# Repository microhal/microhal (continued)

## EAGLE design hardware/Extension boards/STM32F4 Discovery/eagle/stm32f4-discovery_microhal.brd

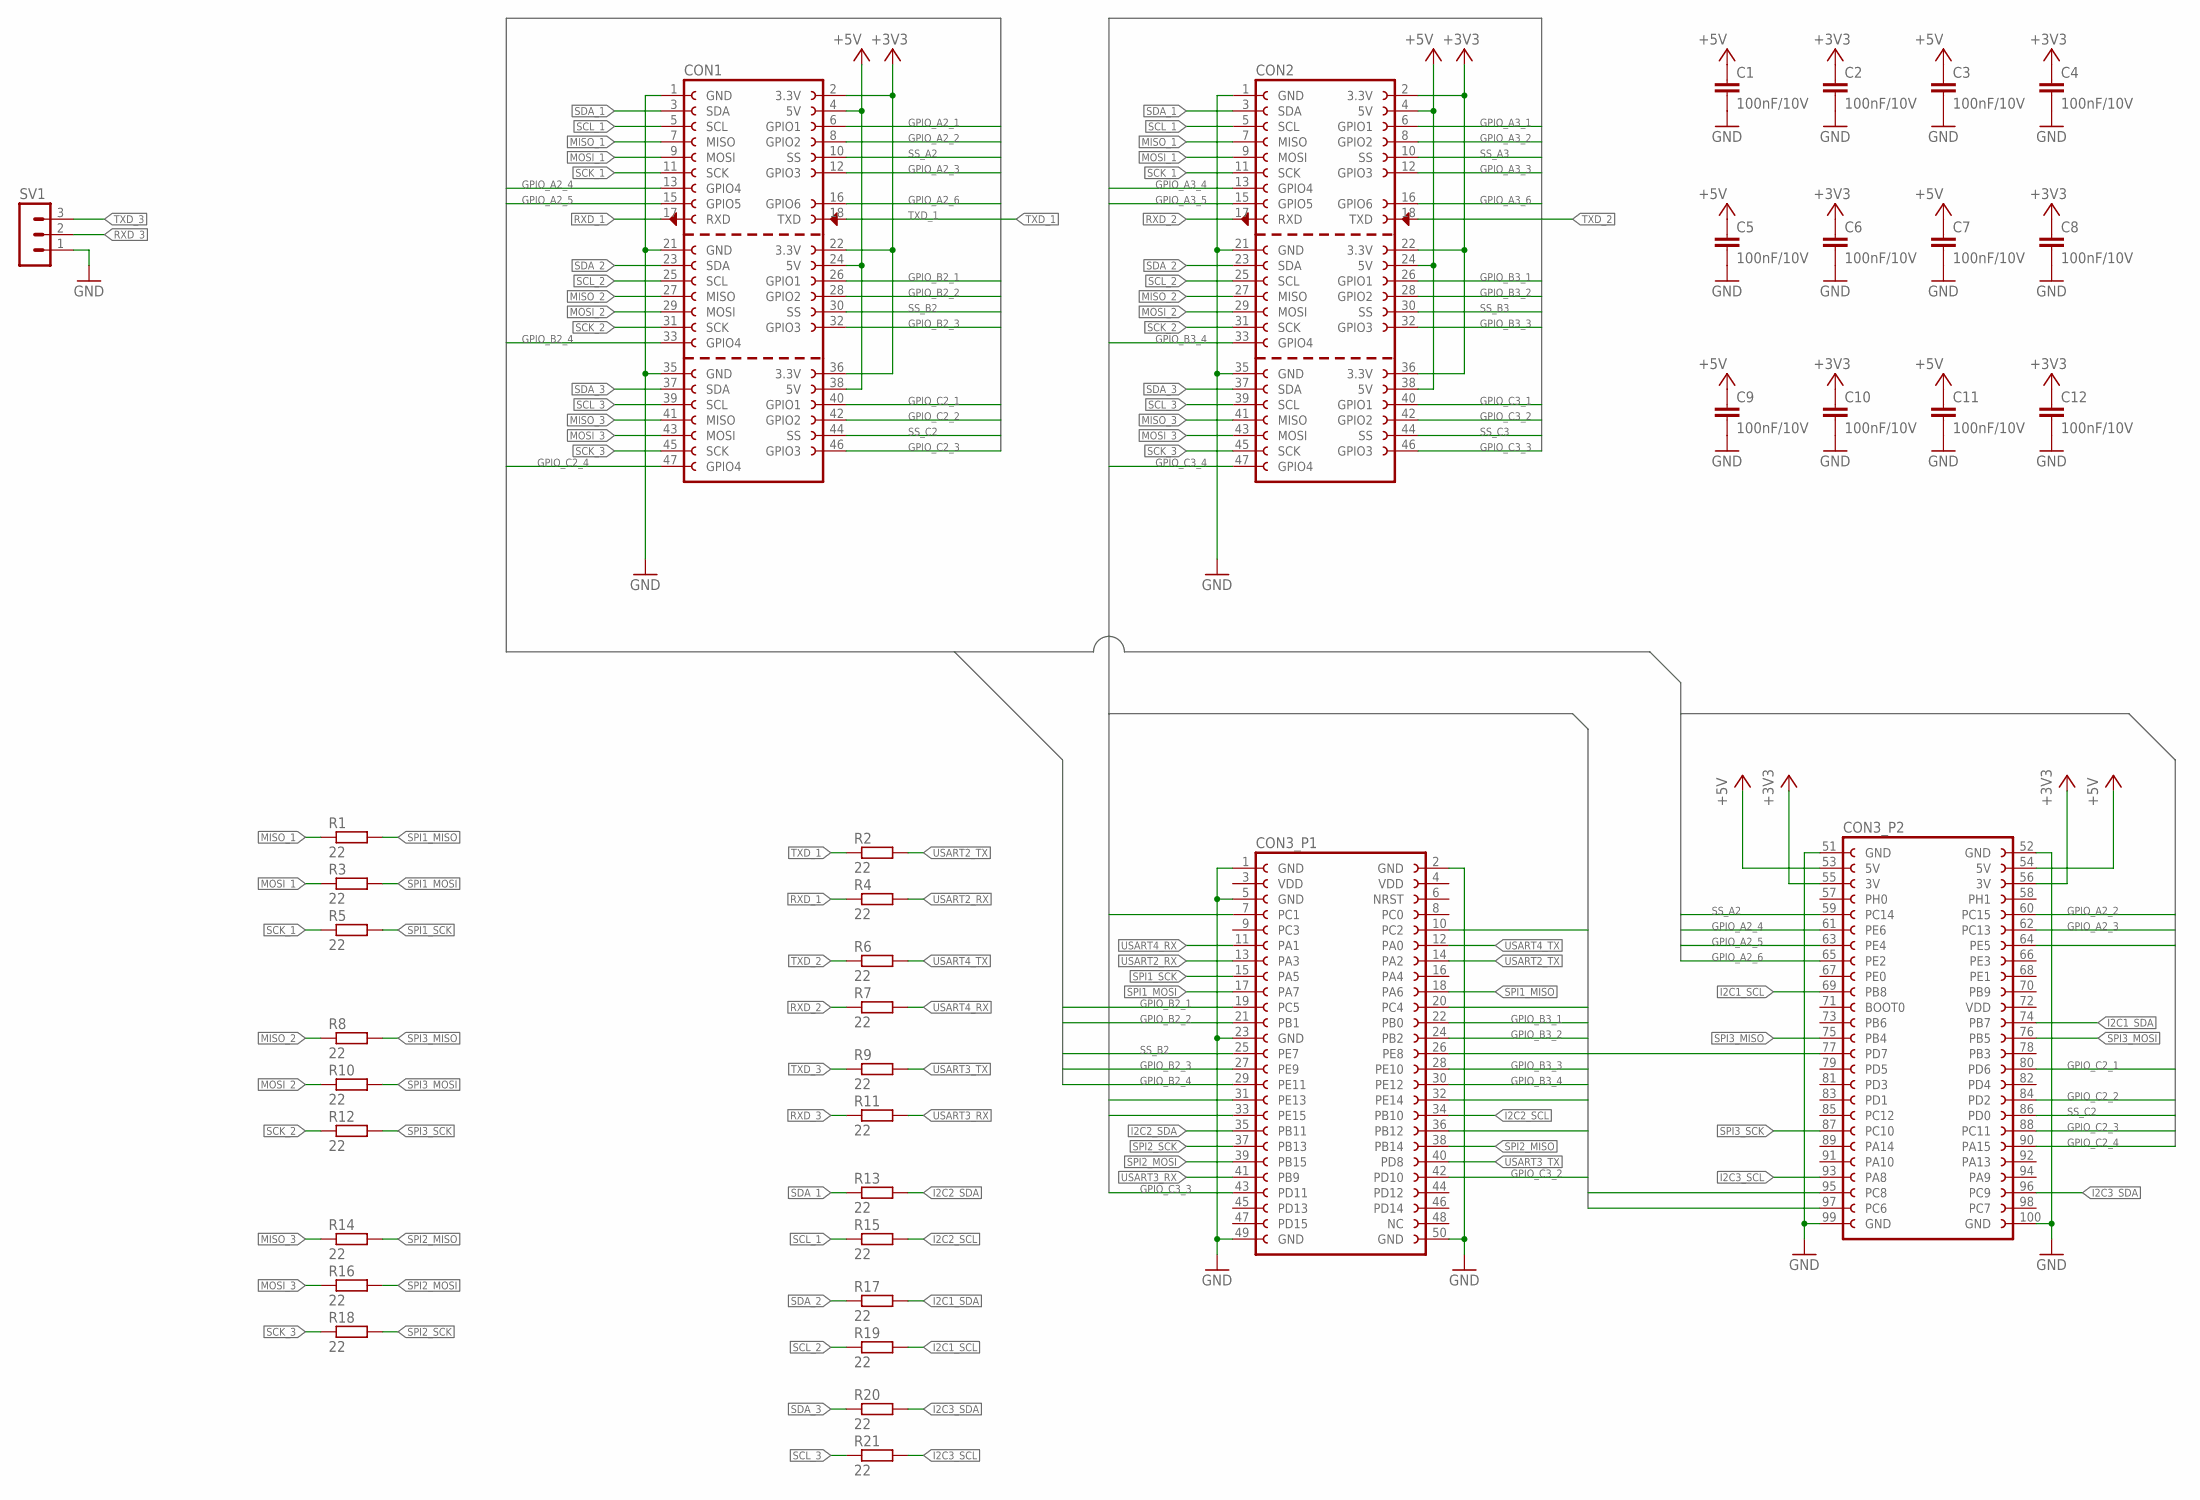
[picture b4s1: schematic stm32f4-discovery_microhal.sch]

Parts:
C1, C2, C3, C4, C5, C6, C7, C8, C9, C10, C11, C12: 100nF/10V; C0603K
CON1, CON2: MICROHAL_CONNECTOR_F_3
CON3: STM32F4DISCOVERY-CONNECTOR; STM32F4DISCOVERY_CONNECTOR
R1, R2, R3, R4, R5, R6, R7, R8, R9, R10, R11, R12, R13, R14, R15, R16, R17, R18, R19, R20, R21: 22; R0603
SV1: MA03-1

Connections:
+3V3: C2.1, C4.1, C6.1, C8.1, C10.1, C12.1, CON1.2 (3.3V), CON1.22 (3.3V), CON1.36 (3.3V), CON2.2 (3.3V), CON2.22 (3.3V), CON2.36 (3.3V), CON3.55 (3V), CON3.56 (3V)
+5V: C1.1, C3.1, C5.1, C7.1, C9.1, C11.1, CON1.4 (5V), CON1.24 (5V), CON1.38 (5V), CON2.4 (5V), CON2.24 (5V), CON2.38 (5V), CON3.53 (5V), CON3.54 (5V)
GND: C1.2, C2.2, C3.2, C4.2, C5.2, C6.2, C7.2, C8.2, C9.2, C10.2, C11.2, C12.2, CON1.1 (GND), CON1.21 (GND), CON1.35 (GND), CON2.1 (GND), CON2.21 (GND), CON2.35 (GND), CON3.1 (GND), CON3.2 (GND), CON3.5 (GND), CON3.23 (GND), CON3.49 (GND), CON3.50 (GND), CON3.51 (GND), CON3.52 (GND), CON3.99 (GND), CON3.100 (GND), SV1.1
GPIO_A2_1: CON1.6 (GPIO1), CON3.64 (PE5)
GPIO_A2_2: CON1.8 (GPIO2), CON3.60 (PC15)
GPIO_A2_3: CON1.12 (GPIO3), CON3.62 (PC13)
GPIO_A2_4: CON1.13 (GPIO4), CON3.61 (PE6)
GPIO_A2_5: CON1.15 (GPIO5), CON3.63 (PE4)
GPIO_A2_6: CON1.16 (GPIO6), CON3.65 (PE2)
GPIO_A3_1: CON2.6 (GPIO1), CON3.97 (PC6)
GPIO_A3_2: CON2.8 (GPIO2), CON3.31 (PE13)
GPIO_A3_3: CON2.12 (GPIO3), CON3.7 (PC1)
GPIO_A3_4: CON2.13 (GPIO4), CON3.10 (PC2)
GPIO_A3_5: CON2.15 (GPIO5), CON3.20 (PC4)
GPIO_A3_6: CON2.16 (GPIO6), CON3.77 (PD7)
GPIO_B2_1: CON1.26 (GPIO1), CON3.19 (PC5)
GPIO_B2_2: CON1.28 (GPIO2), CON3.21 (PB1)
GPIO_B2_3: CON1.32 (GPIO3), CON3.27 (PE9)
GPIO_B2_4: CON1.33 (GPIO4), CON3.29 (PE11)
GPIO_B3_1: CON2.26 (GPIO1), CON3.22 (PB0)
GPIO_B3_2: CON2.28 (GPIO2), CON3.24 (PB2)
GPIO_B3_3: CON2.32 (GPIO3), CON3.28 (PE10)
GPIO_B3_4: CON2.33 (GPIO4), CON3.30 (PE12)
GPIO_C2_1: CON1.40 (GPIO1), CON3.80 (PD6)
GPIO_C2_2: CON1.42 (GPIO2), CON3.84 (PD2)
GPIO_C2_3: CON1.46 (GPIO3), CON3.88 (PC11)
GPIO_C2_4: CON1.47 (GPIO4), CON3.90 (PA15)
GPIO_C3_1: CON2.40 (GPIO1), CON3.32 (PE14)
GPIO_C3_2: CON2.42 (GPIO2), CON3.42 (PD10)
GPIO_C3_3: CON2.46 (GPIO3), CON3.43 (PD11)
GPIO_C3_4: CON2.47 (GPIO4), CON3.95 (PC8)
I2C1_SCL: CON3.69 (PB8), R19.2
I2C1_SDA: CON3.74 (PB7), R17.2
I2C2_SCL: CON3.34 (PB10), R15.2
I2C2_SDA: CON3.35 (PB11), R13.2
I2C3_SCL: CON3.93 (PA8), R21.2
I2C3_SDA: CON3.96 (PC9), R20.2
MISO_1: CON1.7 (MISO), CON2.7 (MISO), R1.1
MISO_2: CON1.27 (MISO), CON2.27 (MISO), R8.1
MISO_3: CON1.41 (MISO), CON2.41 (MISO), R14.1
MOSI_1: CON1.9 (MOSI), CON2.9 (MOSI), R3.1
MOSI_2: CON1.29 (MOSI), CON2.29 (MOSI), R10.1
MOSI_3: CON1.43 (MOSI), CON2.43 (MOSI), R16.1
RXD_1: CON1.17 (RXD), R4.1
RXD_2: CON2.17 (RXD), R7.1
RXD_3: R11.1, SV1.2
SCK_1: CON1.11 (SCK), CON2.11 (SCK), R5.1
SCK_2: CON1.31 (SCK), CON2.31 (SCK), R12.1
SCK_3: CON1.45 (SCK), CON2.45 (SCK), R18.1
SCL_1: CON1.5 (SCL), CON2.5 (SCL), R15.1
SCL_2: CON1.25 (SCL), CON2.25 (SCL), R19.1
SCL_3: CON1.39 (SCL), CON2.39 (SCL), R21.1
SDA_1: CON1.3 (SDA), CON2.3 (SDA), R13.1
SDA_2: CON1.23 (SDA), CON2.23 (SDA), R17.1
SDA_3: CON1.37 (SDA), CON2.37 (SDA), R20.1
SPI1_MISO: CON3.18 (PA6), R1.2
SPI1_MOSI: CON3.17 (PA7), R3.2
SPI1_SCK: CON3.15 (PA5), R5.2
SPI2_MISO: CON3.38 (PB14), R14.2
SPI2_MOSI: CON3.39 (PB15), R16.2
SPI2_SCK: CON3.37 (PB13), R18.2
SPI3_MISO: CON3.75 (PB4), R8.2
SPI3_MOSI: CON3.76 (PB5), R10.2
SPI3_SCK: CON3.87 (PC10), R12.2
SS_A2: CON1.10 (SS), CON3.59 (PC14)
SS_A3: CON2.10 (SS), CON3.33 (PE15)
SS_B2: CON1.30 (SS), CON3.25 (PE7)
SS_B3: CON2.30 (SS), CON3.26 (PE8)
SS_C2: CON1.44 (SS), CON3.86 (PD0)
SS_C3: CON2.44 (SS), CON3.36 (PB12)
TXD_1: CON1.18 (TXD), R2.1
TXD_2: CON2.18 (TXD), R6.1
TXD_3: R9.1, SV1.3
USART2_RX: CON3.13 (PA3), R4.2
USART2_TX: CON3.14 (PA2), R2.2
USART3_RX: CON3.41 (PB9), R11.2
USART3_TX: CON3.40 (PD8), R9.2
USART4_RX: CON3.11 (PA1), R7.2
USART4_TX: CON3.12 (PA0), R6.2

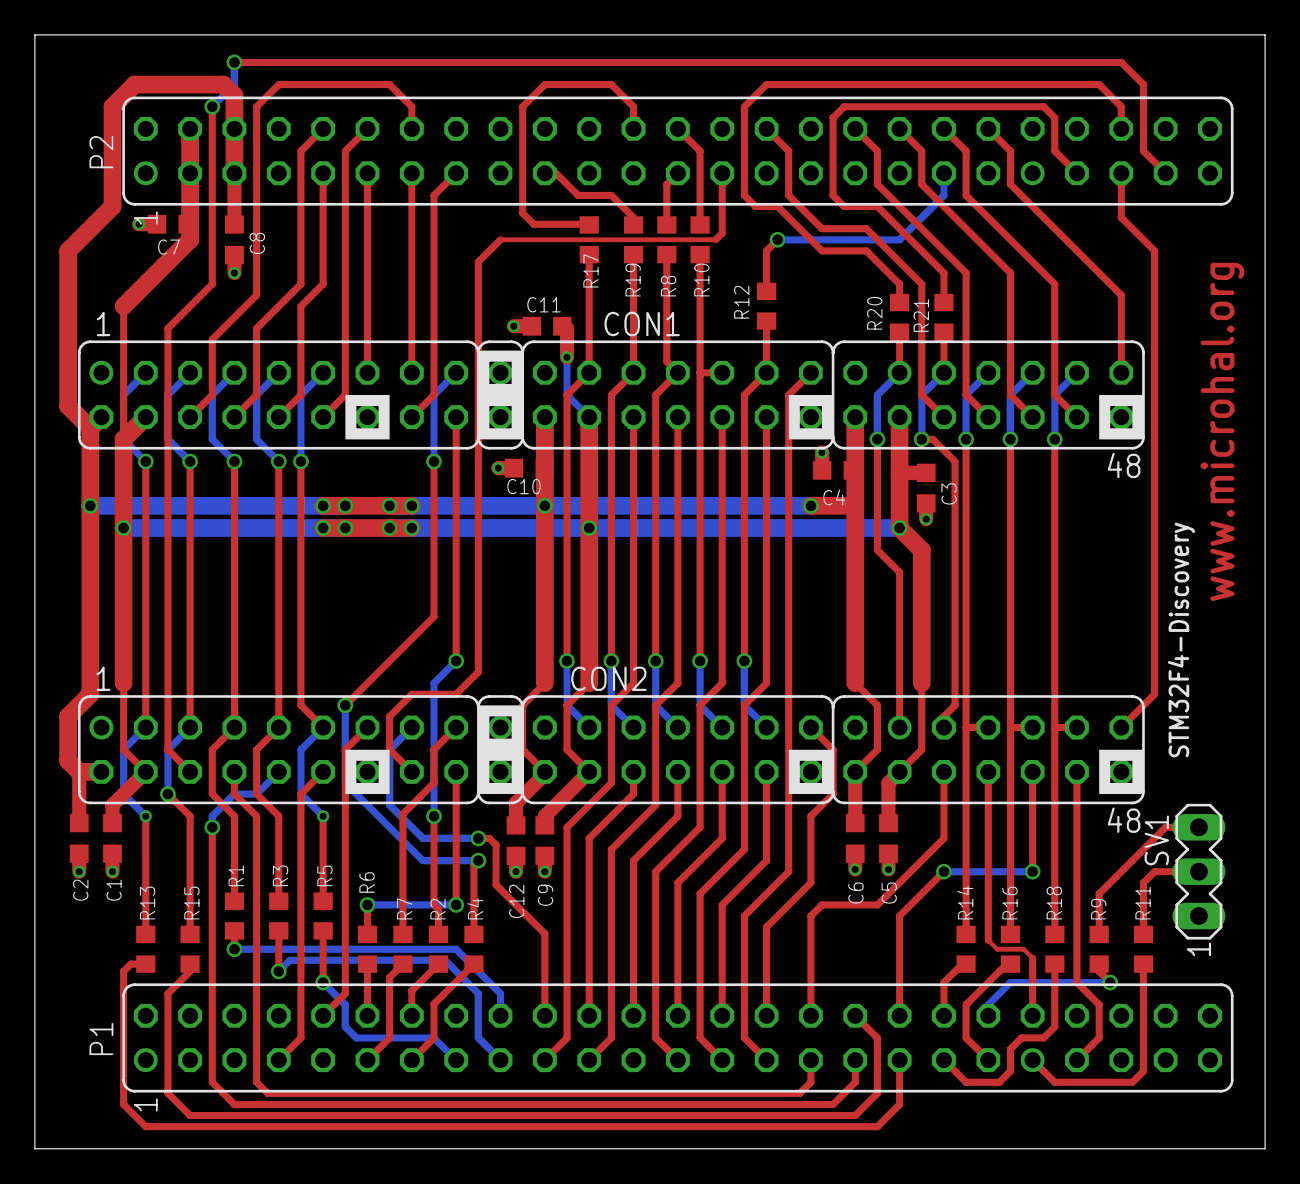
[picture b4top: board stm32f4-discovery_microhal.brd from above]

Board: 2 copper layers, 70.5 x 63.8 mm, 37 parts (0 on the bottom side), 79 nets.

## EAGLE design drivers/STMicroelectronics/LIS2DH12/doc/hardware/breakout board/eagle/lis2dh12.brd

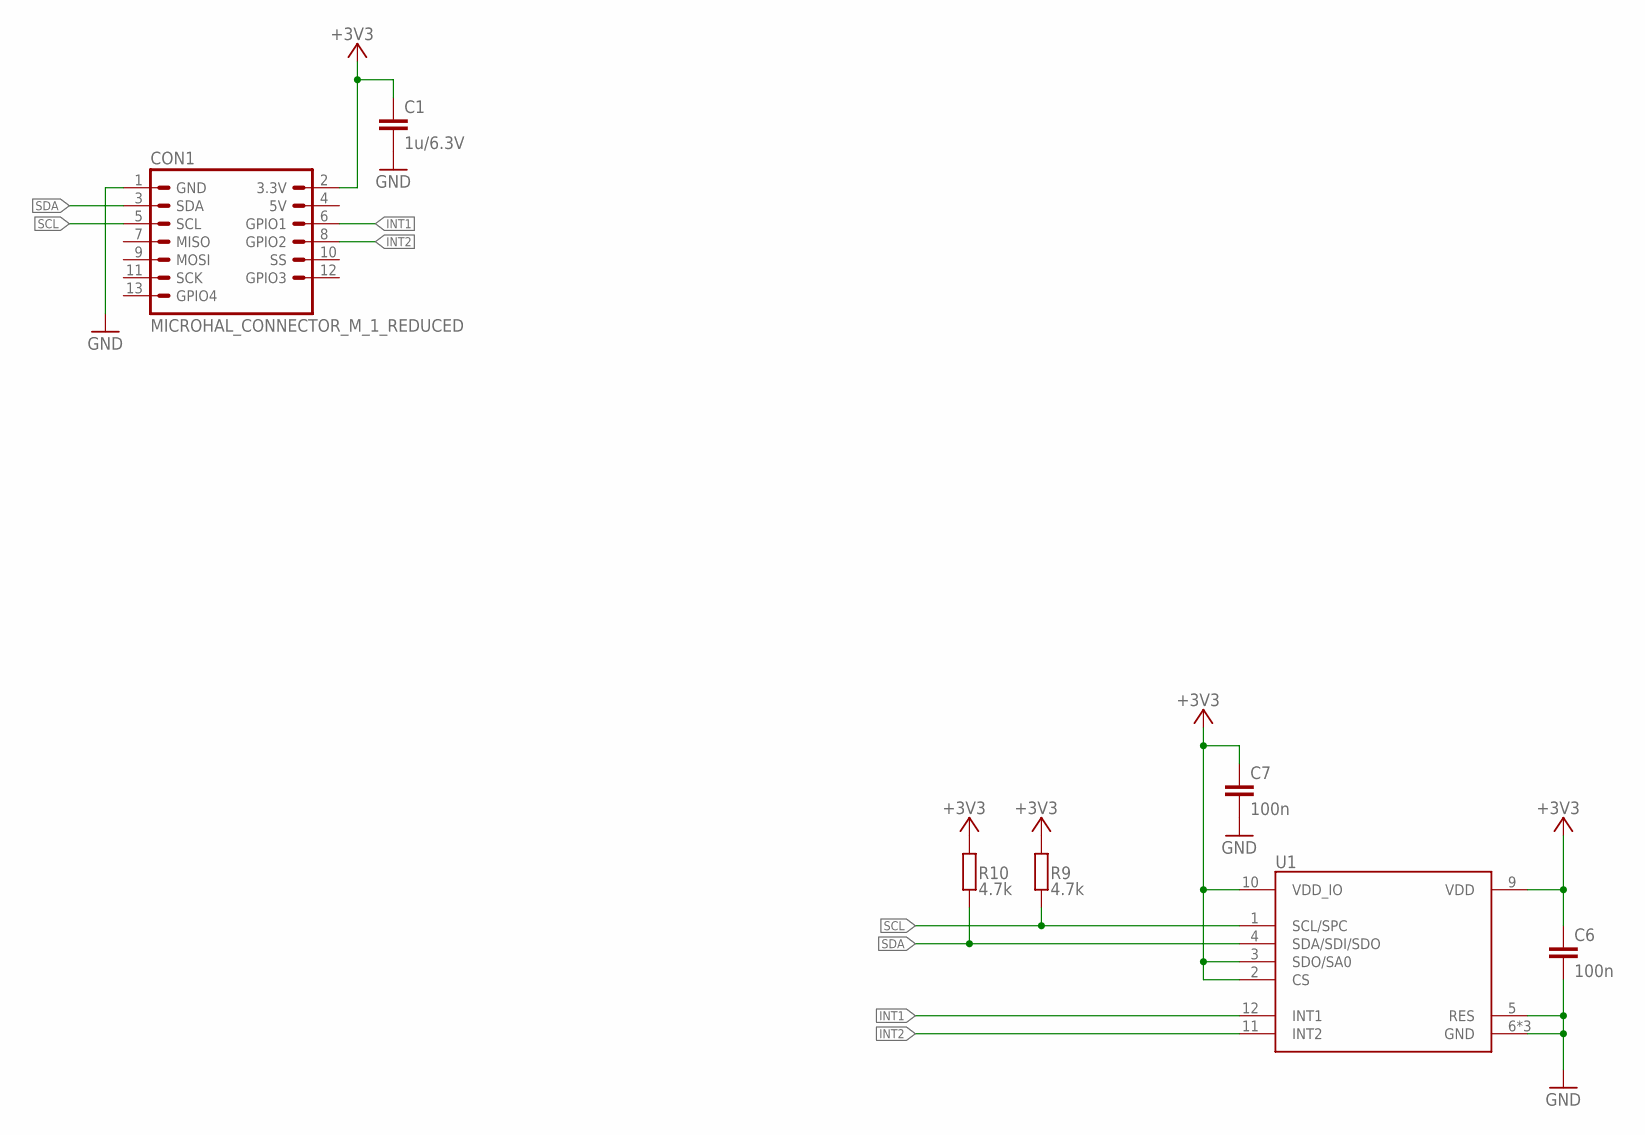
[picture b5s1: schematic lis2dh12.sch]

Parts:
C1: 1u/6.3V; C0603K
C6, C7: 100n; C0603K
CON1: MICROHAL_CONNECTOR_M_1_REDUCED; MICROHAL_CONNECTOR_M_1_REDUCED_EDGE
R9, R10: 4.7k; R0603
U1: LIS2DH12; LGA-12

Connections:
+3V3: C1.1, C6.1, C7.1, CON1.2 (3.3V), R9.1, R10.1, U1.2 (CS), U1.3 (SDO/SA0), U1.9 (VDD), U1.10 (VDD_IO)
GND: C1.2, C6.2, C7.2, CON1.1 (GND), U1.5 (RES), U1.6 (GND), U1.7 (GND), U1.8 (GND)
INT1: CON1.6 (GPIO1), U1.12 (INT1)
INT2: CON1.8 (GPIO2), U1.11 (INT2)
SCL: CON1.5 (SCL), R9.2, U1.1 (SCL/SPC)
SDA: CON1.3 (SDA), R10.2, U1.4 (SDA/SDI/SDO)

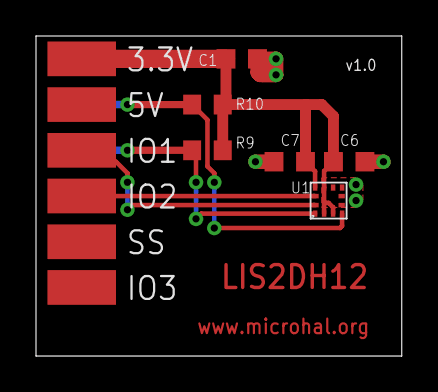
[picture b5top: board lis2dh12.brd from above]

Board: 2 copper layers, 20.3 x 17.8 mm, 7 parts (0 on the bottom side), 6 nets.

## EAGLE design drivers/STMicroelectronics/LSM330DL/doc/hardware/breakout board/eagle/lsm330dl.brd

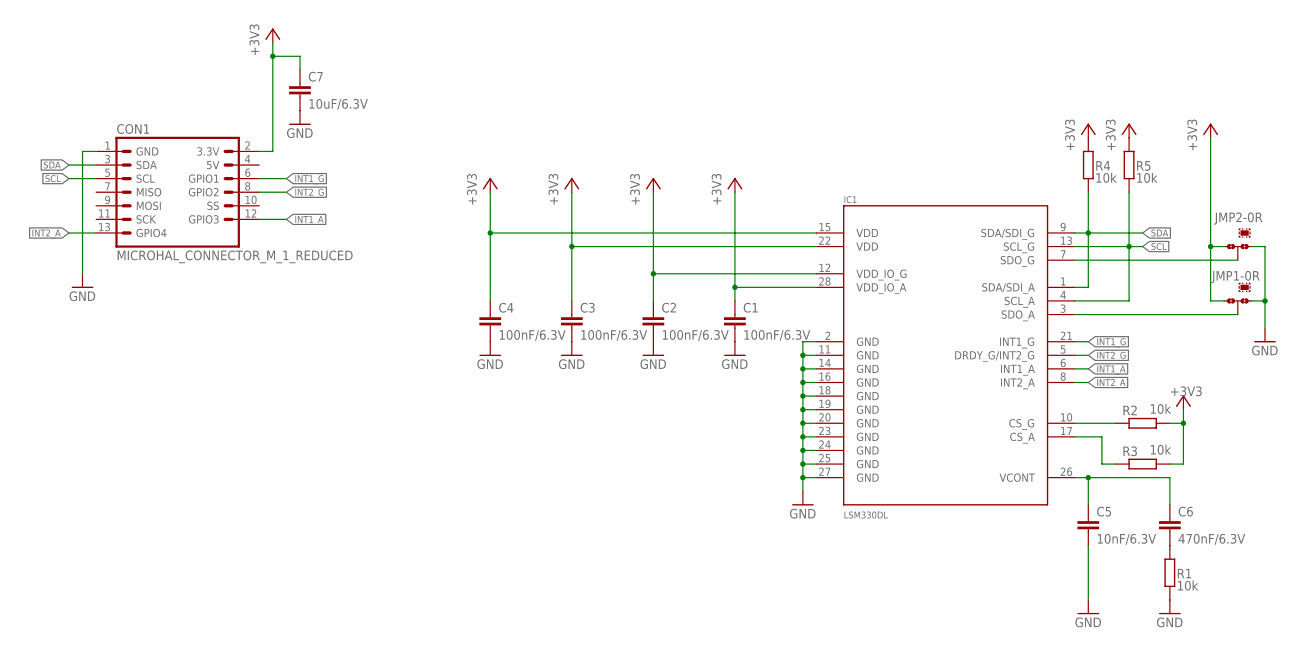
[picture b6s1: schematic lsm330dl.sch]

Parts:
C1, C2, C3, C4: 100nF/6.3V; C0402K
C5: 10nF/6.3V; C0402K
C6: 470nF/6.3V; C0402K
C7: 10uF/6.3V; C0805K
CON1: MICROHAL_CONNECTOR_M_1_REDUCED; MICROHAL_CONNECTOR_M_1_REDUCED_EDGE
IC1: LSM330DL; LGA7.5X4.4_28L
JMP1, JMP2: 0R-JUMPC; C0R-JMP
R1, R2, R3, R4, R5: 10k; R0402

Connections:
+3V3: C1.1, C2.1, C3.1, C4.1, C7.1, CON1.2 (3.3V), IC1.12 (VDD_IO_G), IC1.15 (VDD), IC1.22 (VDD), IC1.28 (VDD_IO_A), JMP1.3, JMP2.3, R2.1, R3.1, R4.2, R5.2
GND: C1.2, C2.2, C3.2, C4.2, C5.2, C7.2, CON1.1 (GND), IC1.2 (GND), IC1.11 (GND), IC1.14 (GND), IC1.16 (GND), IC1.18 (GND), IC1.19 (GND), IC1.20 (GND), IC1.23 (GND), IC1.24 (GND), IC1.25 (GND), IC1.27 (GND), JMP1.1, JMP2.1, R1.1
INT1_A: CON1.12 (GPIO3), IC1.6 (INT1_A)
INT1_G: CON1.6 (GPIO1), IC1.21 (INT1_G)
INT2_A: CON1.13 (GPIO4), IC1.8 (INT2_A)
INT2_G: CON1.8 (GPIO2), IC1.5 (DRDY_G/INT2_G)
unnamed: C6.2, R1.2
unnamed: C5.1, C6.1, IC1.26 (VCONT)
unnamed: IC1.17 (CS_A), R3.2
unnamed: IC1.10 (CS_G), R2.2
unnamed: IC1.3 (SDO_A), JMP1.2
unnamed: IC1.7 (SDO_G), JMP2.2
SCL: CON1.5 (SCL), IC1.4 (SCL_A), IC1.13 (SCL_G), R5.1
SDA: CON1.3 (SDA), IC1.1 (SDA/SDI_A), IC1.9 (SDA/SDI_G), R4.1

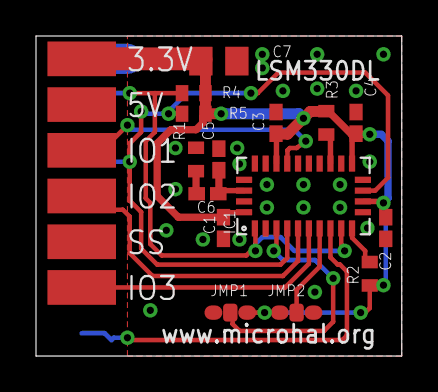
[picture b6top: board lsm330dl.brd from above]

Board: 2 copper layers, 20.3 x 17.8 mm, 16 parts (0 on the bottom side), 14 nets.

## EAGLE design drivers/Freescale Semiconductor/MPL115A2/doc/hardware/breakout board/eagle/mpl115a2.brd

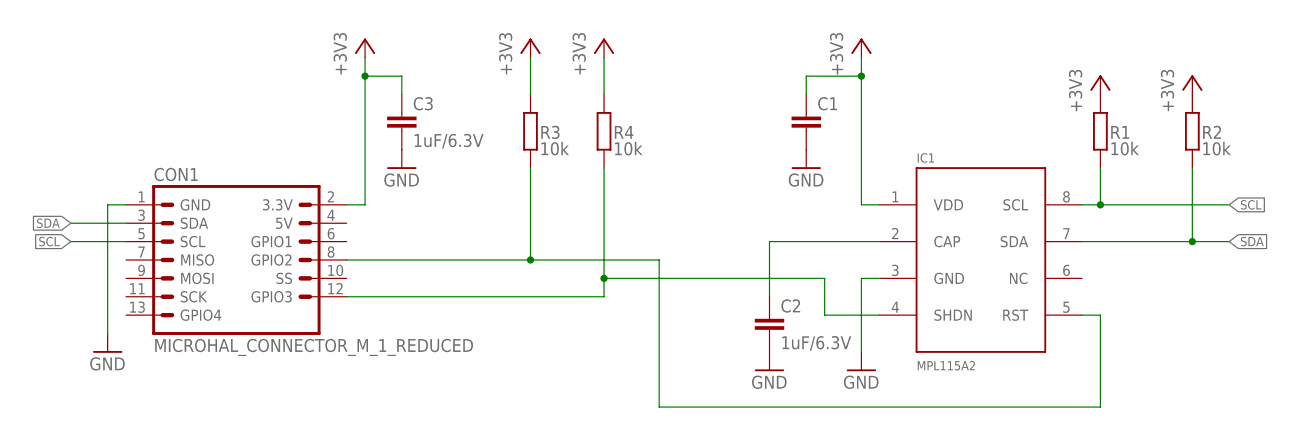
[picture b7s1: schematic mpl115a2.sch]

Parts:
C1: C-EUC0603K; C0603K
C2, C3: 1uF/6.3V; C0603K
CON1: MICROHAL_CONNECTOR_M_1_REDUCED; MICROHAL_CONNECTOR_M_1_REDUCED_EDGE
IC1: MPL115A2
R1, R2, R3, R4: 10k; R0603

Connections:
+3V3: C1.1, C3.1, CON1.2 (3.3V), IC1.1 (VDD), R1.2, R2.2, R3.2, R4.2
GND: C1.2, C2.2, C3.2, CON1.1 (GND), IC1.3 (GND)
unnamed: CON1.12 (GPIO3), IC1.4 (SHDN), R4.1
unnamed: C2.1, IC1.2 (CAP)
unnamed: CON1.8 (GPIO2), IC1.5 (RST), R3.1
SCL: CON1.5 (SCL), IC1.8 (SCL), R1.1
SDA: CON1.3 (SDA), IC1.7 (SDA), R2.1

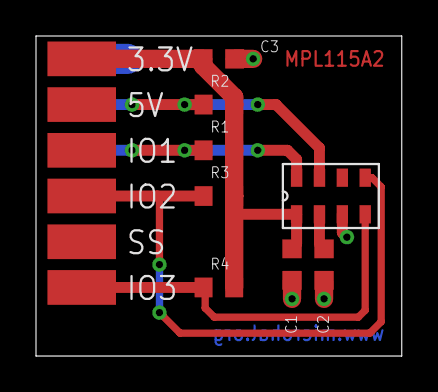
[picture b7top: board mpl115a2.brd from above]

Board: 2 copper layers, 20.3 x 17.8 mm, 9 parts (0 on the bottom side), 7 nets.

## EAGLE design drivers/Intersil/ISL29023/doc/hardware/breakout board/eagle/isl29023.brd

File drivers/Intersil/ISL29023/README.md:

# ISL29023
Integrated Digital Light Sensor with Interrupt

[Documentation PDF](http://www.intersil.com/content/dam/Intersil/documents/isl2/isl29023.pdf)

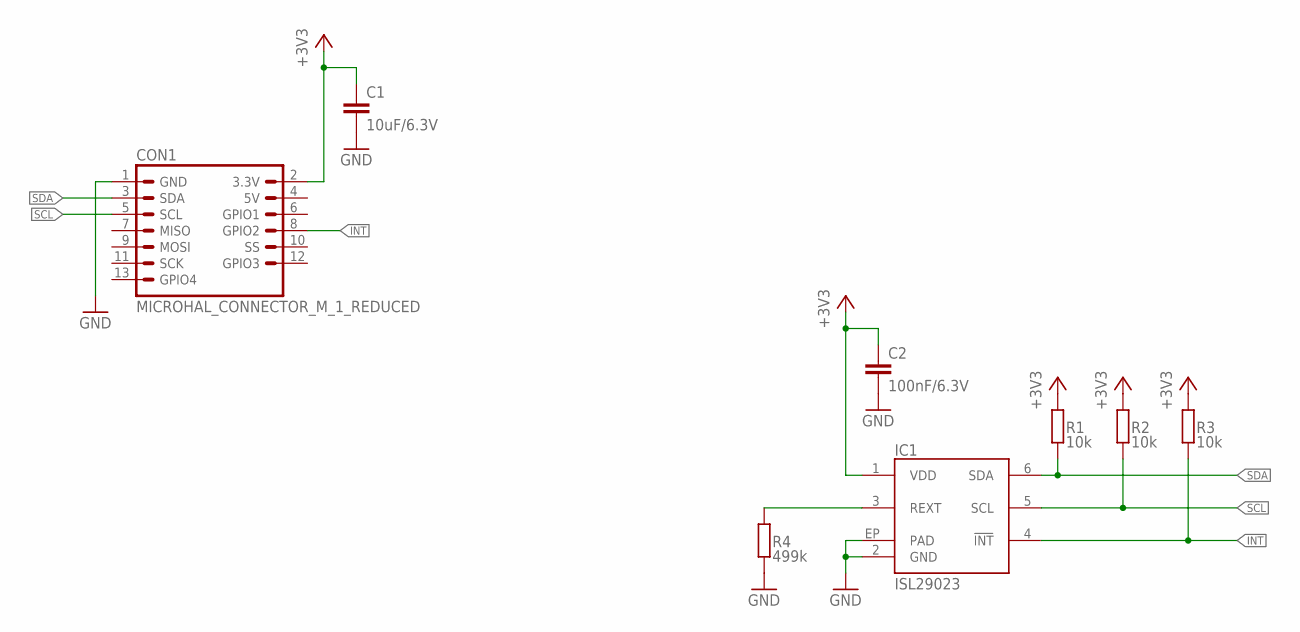
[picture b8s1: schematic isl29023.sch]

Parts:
C1: 10uF/6.3V; C0805K
C2: 100nF/6.3V; C0603K
CON1: MICROHAL_CONNECTOR_M_1_REDUCED; MICROHAL_CONNECTOR_M_1_REDUCED_EDGE
IC1: ISL29023; ODFN-6
R1, R2, R3: 10k; R0603
R4: 499k; R0603

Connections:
+3V3: C1.1, C2.1, CON1.2 (3.3V), IC1.1 (VDD), R1.2, R2.2, R3.2
GND: C1.2, C2.2, CON1.1 (GND), IC1.2 (GND), IC1.EP (PAD), R4.1
INT: CON1.8 (GPIO2), IC1.4 (!INT), R3.1
unnamed: IC1.3 (REXT), R4.2
SCL: CON1.5 (SCL), IC1.5 (SCL), R2.1
SDA: CON1.3 (SDA), IC1.6 (SDA), R1.1

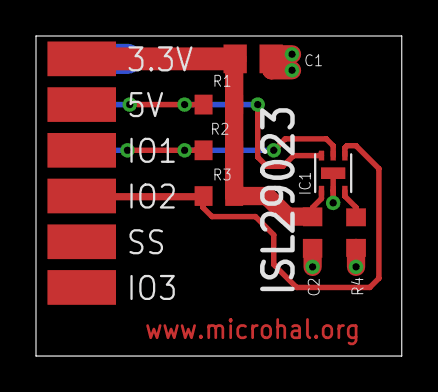
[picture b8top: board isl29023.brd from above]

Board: 2 copper layers, 20.3 x 17.8 mm, 8 parts (0 on the bottom side), 6 nets.

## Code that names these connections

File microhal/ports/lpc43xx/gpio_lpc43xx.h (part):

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                                                       1 * 32 + 20   // GPIO0[15]
                                                   },
                                                   {
                                                       1 * 32 + 7,   // GPIO1[0]
                                                       1 * 32 + 8,   // GPIO1[1]
                                                       1 * 32 + 9,   // GPIO1[2]
                                                       1 * 32 + 10,  // GPIO1[3]
                                                       1 * 32 + 11,  // GPIO1[4]
                                                       1 * 32 + 12,  // GPIO1[5]
                                                       1 * 32 + 13,  // GPIO1[6]
                                                       1 * 32 + 14,  // GPIO1[7]
                                                       1 * 32 + 5,   // GPIO1[8]
                                                       1 * 32 + 6,   // GPIO1[9]
                                                       2 * 32 + 9,   // GPIO1[10]
                                                       2 * 32 + 11,  // GPIO1[11]
                                                       2 * 32 + 12,  // GPIO1[12]
                                                       2 * 32 + 13,  // GPIO1[13]
                                                       3 * 32 + 4,   // GPIO1[14]
                                                       3 * 32 + 5    // GPIO1[15]

                                                   },
                                                   {
                                                       4 * 32 + 0,   // GPIO2[0]
                                                       4 * 32 + 1,   // GPIO2[1]
                                                       4 * 32 + 2,   // GPIO2[2]
                                                       4 * 32 + 3,   // GPIO2[3]
                                                       4 * 32 + 4,   // GPIO2[4]
                                                       4 * 32 + 5,   // GPIO2[5]
                                                       4 * 32 + 6,   // GPIO2[6]
                                                       5 * 32 + 7,   // GPIO2[7]
                                                       6 * 32 + 12,  // GPIO2[8]
                                                       5 * 32 + 0,   // GPIO2[9]
                                                       5 * 32 + 1,   // GPIO2[10]
                                                       5 * 32 + 2,   // GPIO2[11]
                                                       5 * 32 + 3,   // GPIO2[12]
                                                       5 * 32 + 4,   // GPIO2[13]
                                                       5 * 32 + 5,   // GPIO2[14]
                                                       5 * 32 + 6,   // GPIO2[15]
                                                   },
                                                   {
                                                       6 * 32 + 1,   // GPIO3[0]
                                                       6 * 32 + 2,   // GPIO3[1]
                                                       6 * 32 + 3,   // GPIO3[2]
                                                       6 * 32 + 4,   // GPIO3[3]
                                                       6 * 32 + 5,   // GPIO3[4]
                                                       6 * 32 + 9,   // GPIO3[5]
                                                       6 * 32 + 10,  // GPIO3[6]
                                                       6 * 32 + 11,  // GPIO3[7]
                                                       7 * 32 + 0,   // GPIO3[8]
                                                       7 * 32 + 1,   // GPIO3[9]
                                                       7 * 32 + 2,   // GPIO3[10]
                                                       7 * 32 + 3,   // GPIO3[11]
                                                       7 * 32 + 4,   // GPIO3[12]
                                                       7 * 32 + 5,   // GPIO3[13]
                                                       7 * 32 + 6,   // GPIO3[14]
                                                       7 * 32 + 7,   // GPIO3[15]
                                                   },
                                                   {
                                                       8 * 32 + 0,   // GPIO4[0]
                                                       8 * 32 + 1,   // GPIO4[1]
                                                       8 * 32 + 2,   // GPIO4[2]
                                                       8 * 32 + 3,   // GPIO4[3]
                                                       8 * 32 + 4,   // GPIO4[4]
                                                       8 * 32 + 5,   // GPIO4[5]
                                                       8 * 32 + 6,   // GPIO4[6]
                                                       8 * 32 + 7,   // GPIO4[7]
                                                       10 * 32 + 1,  // GPIO4[8]
                                                       10 * 32 + 2,  // GPIO4[9]
                                                       10 * 32 + 3,  // GPIO4[10]
                                                       9 * 32 + 6,   // GPIO4[11]
                                                       9 * 32 + 0,   // GPIO4[12]
                                                       9 * 32 + 1,   // GPIO4[13]
                                                       9 * 32 + 2,   // GPIO4[14]
                                                       9 * 32 + 3,   // GPIO4[15]
                                                   }};

    static GpioPin getGpioPinFromIOPin(IOPin pin) {
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
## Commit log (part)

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2020-04-16 Port STM Common, updated clock enable in i2c v1 driver.
2020-04-16 Graphics added font interface.
2020-04-17 Port STM32F3xx, added driver configuration file.
2020-05-04 Port STMCommon, updated clocks manager for: hse, lsi, lse.
2020-05-04 Port STM32F3xx, removed ioPin.h, switched to using ioPin from stmCommon.
2020-05-04 Port STM32F3xx, updated driver configuration macros.
2020-05-05 Port STMCommon, added macros to select adc driver version.
2020-05-05 Port STMCommon, added macro comments in ADC clock manager.
2020-05-05 Port STM32F3xx, updated timer driver.
2020-05-05 Units, added voltage unit.
2020-05-10 Port STMCommon, updated serial port selection preprocesor macros in serial port v1 driver.
2020-05-10 Port STMCommon, added driver selection macros for I2C v1.
2020-11-07 Linux port, updated can implementation.
2020-11-07 Port STM32F103 added CAN port.
2020-11-07 Port STMCommon, CAN driver added preprocessor switches for different mcu types.
2020-11-19 Added operator== into CAN::Filter
2020-11-25 Added CAN over Hostcomm component.
2020-11-26 Updated serial port test.
2020-11-26 Components - CAN over Hostcomm, added unit tests and unit test project.
2020-11-26 Core - IODevice, changed mutex type to recursive_timed_mutex.
2020-11-26 Core - IODevice, added virtual IODevice.
2020-11-28 Port Linux, serialPort added getPortName method and getSerialPortList method.
2020-11-28 Core - Diagnostic, changed implementation of endl(), now endl methode writes different characters depending on operating system macro.
2020-12-02 Port STMCommon, updated timer v1 driver.
2020-12-04 Core, added volatile register added spetialization for uint32_t.
2020-12-09 Third-party, updated FreeRTOS submodule.
2020-12-09 Core, moved iodevice into IODevice directory.
2020-12-09 Updated include paths and gpio function.
2020-12-09 Port stm32f103xx, updated driver configuration file, added DMA and ADC version specification.
2020-12-09 Components GPS, added geters.
2020-12-11 Updated driver example: M24C16, SHT21, updated bsp and eclipse project.
2020-12-11 Port STM32F0xx, updated includes in I2C related headers.
2020-12-11 Port STMCommon - I2C v2, updated macro #if checking.
2020-12-11 Port STMCommon - clock manager, added RTC functions.
2020-12-11 Updated port manager.
2020-12-11 Port STMCommon - ADC v2, added missing include
2021-02-03 Port STM32F3xx and STM32F4xx, added clockManager.h
2021-02-03 Updated device drivers examples.
2021-02-03 Updated gpio driver.
2021-02-03 Port STM32F1xx, updated IOManager, nvic, syscalls.
2021-02-03 Port STMCommon, added function for conversion adc voltage into temperature in celsius for internal temperature sensor.
2021-02-03 Port STMCommon, updated SPI driver.
2021-02-03 Port STM32F1xx, updated startup and added mcuCapabilities file.
2021-02-04 Port STM32GXX, added initial files for port.
2021-02-04 Port STM32G0XX, added register base address definitions.
2021-02-04 Port STM32F1xx, updated mcuCapabilities
2021-02-06 Port STM32G0XX, added I2C and watchdog.
2021-02-06 Drivers, added nucleo-g071rb into SHT21 example.
2021-02-10 Port STMCommon, STM32G0xx, Added PWR version 2.
2021-02-10 Port STMCommon, updated pll clock manager.
2021-02-10 MRF89XA added configuratiion for Nucleo-g071rb.
2021-02-11 Port STMCommon, clock manager updated rcc registers include.
2021-02-16 Port STM32G0xx and STMCommon, added tamper and backup register driver.
2021-02-19 Port STMCommon, ClockManager added #include 'rcc_register_select.h'
2021-02-19 Port STMCommon, updated DMA v1 driver to work with STM32G0xx.
2021-02-19 Port STMCommon, serialPort v1, added LIN functions.
2021-02-27 Drivers, added driver for RFM96 Radio module.
2021-02-28 Utils types, changed endianness of microhal::uint24_t to little.
2021-02-28 SPIDevice, changed address parameter to use devicerRegister objects as registers.
2021-02-28 Device drivers, RFM96HCW added reset and dio0 gpio into constructor, added dio0 ISR into class.
2021-03-01 Port STMCommon, RTC v2, added support for linux epoch.
2021-03-02 Port STMCommon, RTC v2, fixed setEpoch method.
2021-03-02 Port STM32G0xx, implemented UniqueID read methods in hardware::Device class.
2021-03-04 Port STMCommon, PWR v2, added wakeup pin control functions.
2021-03-04 HostComm, updated include path
2021-03-10 Drivers RFM96, added static function for calculating packet send time.
2021-03-11 Drivers RFM96, added global variable maxSckFrequency_Hz.
2021-03-12 SPIDevice added common write_noLock method, added readRegister_noLock_impl methode.
2021-03-14 Added basic LIN communication support.
2021-03-14 Updated LIN, added request method. Added sendBreak parameter into write method.
2021-03-18 Port STMCommon, ADC v1, added sampling time configuration functions, added prescaler configuration method.
2021-03-20 OS & FreeRTOS port, added support for microhal::os with therad name, stack size and priority paramters.
2021-03-21 Port STMCommon, clockManager, SPI clock added support for devices without APB2.
2021-03-27 Port STMCommon, timer v1, moved constructor and destruction into .cpp, moved getTimerClockSourceFrequency(), getTimerCounterFrequency(), getTickPeriod(), getNumber() into .cpp. Added enableOnePulseMo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
2021-03-27 Port STM32G0xx, added timer implementation.
2021-03-27 Ports STMCommon, added syscfg register.
2021-03-27 Port STM32G0xx, added asserts into interruptController.
2021-03-27 Port STMCommon, serialPort v1 is now using interruptController.
2021-03-30 Port STMCommon, LIN v1, updated to use interrupt controller. Increased buffer size.
2021-03-31 Port STMCommon, LIN v1 updated interrupt function.
2021-04-02 Port STMCommon, RTC v2 added static const variables for max values of synchronous and asynchronous prescallers.
2021-04-02 Port STMCommon, SPI v1, fixed speed().
2021-04-02 Drivers RFM96, fixed reset(), improved fifo access.
2021-04-09 Port STMCommon, RTC v2, added smoothDigitalCallibration method.
2021-04-09 Port STM32F1xx and STMCommon, updated STM32F1xx port to support interrupt controller.
2021-04-10 Port STMCommon, clock manager added support for CAN2.
2021-04-10 Port STMCommon, moved CAN constructor to .cpp file.
2021-04-21 OS port noRTOS, improved (sleep for) delay functions.
2021-04-21 Port STMCommon, RTC v2, fixed assert in subSecondCalibrate, added assert to smoothDigitalCalibration().
2021-04-21 Port STM32G0xx, fixed register capability macro for CCIPR.
2021-04-30 GPS, fixed throwing out of range while geting substr in functions: decodeLatitude, decideLongitude, isChecksumValid, fixed return value from decode functions.
2021-04-30 Port STM32F4xx, SPI switched to driver from STMCommon.
2021-04-30 Port STM32F3xx, timer switched to driver from STMCommon.
2021-04-30 Port STMCommon, RTC v2 fixed compilation for other ports than stm32g0xx by removing unnecesary namespace.
2021-04-30 Port STM32F3xx, STM32F4xx, added interrupt controller.
2021-04-30 Port STMCommon, ClockManager added operator| to PowerMode.
2021-04-30 Graphics added triangle class.
2021-04-30 Tools added expansion header file generator.
2021-04-30 Port STM32F4xx, STM32F3xx, updated IOManager.
2021-05-04 Removed CRC lib.
2021-05-04 Updated diagnostic hearer generator to work with new crc library.
2021-05-12 Port STMCommon, Clock Manager, PLL v2 added preprocesor macro detecting presence of R bitfields and Pll output bitfields.
2021-05-13 Small changes that allow serial port and ticToc examples to build.
2021-05-14 Port STM32F1XX, interrupt controller added support for stm32f107, added CAN and USB interrupts management.
2021-05-14 Port STMCommon, PLL v1 added support for PLL2 and PLL3 (present in STM32F107).
2021-05-18 Port STMCommon, clock manager, added ethernet clock; usb otg clock; hclk clock; updated mco clock output control.
2021-05-18 Port STMCommon, added ethernet driver.
2021-05-18 Port STMCommon, STM32F1XX, Clock manager PLL v1, Added macros for detection if PLL2 and PLL3 are present.
2021-05-21 Updated hostcomm submodule to latest version.
2021-05-22 CLI, updated includes.
2021-05-22 Added CLI as submodule.
2021-05-24 Port STM32F1XX, moved rcc files into rcc directory.
2021-05-26 Port Linix spi_linux.h changed cast style from C to C++.
2021-05-26 Port Linux, SerialPort added default variable initialization. Disabled copying.
2021-05-27 Common types, added asUint32_tNetworkEndianness to ip type.
2021-05-28 Updated cli component.
2021-05-28 Added SocketIODevice.
2021-05-28 Port STMCommon, GPIO v1, extracted GPIOPort class to separate file.
2021-05-28 Port STM32F1XX Updated iomanager.
2021-05-29 GPIO Interface, changed functions signature, changed/added returning error from functions, used negative int for error information.
2021-06-01 Port STMCommon, GPIO v1, updated to new GPIO API.
2021-06-01 Changed IODevice funtion return types.
2021-06-02 Port STM32F1xx, added Ethernet flags into mcuCapabilities
2021-06-02 Port STM32F1xx, updated clock manager.
2021-06-02 Port STMCommon, ADC v2, getTemperatureSensorChannel and getInternalRererenceChannel made static.
2021-06-02 Ports common, updated serialPort_bufferedBase to work with new IODevice API.
2021-06-02 port STMC32F1xx, interruptControler for stm32f103 added CAN and Timers interrupt.
2021-06-08 Port STM32G0xx, updated IOManager to latest GPIO API, Added macro into RCC register.
2021-06-09 Driver Display SSD1306, Added concepts to enable constructors, added rotate method. Fixed I2C implementation.
2021-06-17 Test, added SPI Test project files.
2021-06-19 Added cpputest as submodule.
2021-06-20 Moved syscalls test into FatFsConenctor.
2021-06-22 Component FatFsConnector, fixed syscall _isatty_r and _read.
2021-06-22 Components SDCard, updated tests to work with cpputest
2021-06-22 Port STM32F4xx, updated interrupt controller.
2021-06-22 Port STMCommon, STM32G0xx: Added DMA MUX.
2021-06-22 Port STM32G0xx, added spi dma implementation.
2021-06-22 Port STM32F4xx, DMA added HAS_BANKS preprocesor definition.
2021-06-22 Port STM32G0xx, updated rcc, added define: _MICROHAL_REGISTERS_RCC_PLLCFGR_HAS_ENABLE_OUTPUT
2021-06-22 Utils volatileRegister, added volatileLoad_8bit().
2021-06-22 Components FatFsConnector, added disk format type parameter into format function.
2021-06-23 SPI Interface, added maxCLKFrequency().
2021-06-23 Components FatFsConnector, added checking if max CLK frequency was set correctly.
2021-06-23 Port stmCommon, SPI v1, changed behaviour of speed setter function, set frequency will be less or equal than requested.
2021-06-23 Updated microhal-os submodule to latest version.
2021-07-15 Device driver, added ADF4360 driver.
2021-09-04 Port STMCommon, LIN v1 added support for USART6.
2021-09-05 Moved demo projects directory into separate demo-projects repository.
2021-09-06 Updated GPIO API, now using microhal Expecded to return function results. Updated STM32xx GPIO port to work with new api. Updated gpio example to work with new API. Updated DataBus class to work with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
2021-09-07 Port STMCommon, fixed namespace name in interuptController.h
2021-09-07 Port STM32F4xx, changed interrupt controller to use 'interruptController.h' from stmCommon directory.
2021-09-13 Port STMCommon, fixed LIN implementation.
2021-09-13 Port STM32G0xx, interruptController, updated USART number parameter in USART functions form uint8_t to uint_fast8_t.
2021-09-15 Core LIN Frame, changed method of storing frame parameters. Now all frame parameter are stored in single array.
2021-09-15 Port Linux, updated I2C driver.
2021-09-15 Port STM32F4xx, added spiMaxCLKFrequency into mcuCapabilities.h
2021-09-15 Port STMCommon Timer v1, updated regisers definition to work with STM32G0xx.
2022-01-26 Port Linux, updated GPIO driver to new GPIO Interface.
2022-01-26 Port Manage, updated path after renaming Linux generic directory.
2022-01-29 SerialPort example, added bsp for nucleo-g071rb, modified serial port name.
2022-01-30 IOManager, Changed API.
2022-01-30 Port stmCommon, added common IOManager files.
2022-01-30 Tools, added pin info for stm32f103x8 and stm32f103xB
2022-04-26 Updated GPIO mock and linux driver.
2023-04-28 Moved FatFsConnector to separate repository.
2023-04-28 Moved component GPS to separate repository.
2023-04-28 Removed cli submodule.
2023-04-28 Moved math library to separate repository.
2023-06-10 Linux port - added ADC, fixed IOPin and consoleIODevice error when linux is defined
